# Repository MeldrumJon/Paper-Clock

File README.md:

# Paper-Clock

Minimalistic clock with an e-ink display.

## Components

- [Enclosure](./3D)
- [PCB](./hardware)
- [Firmware](./src)

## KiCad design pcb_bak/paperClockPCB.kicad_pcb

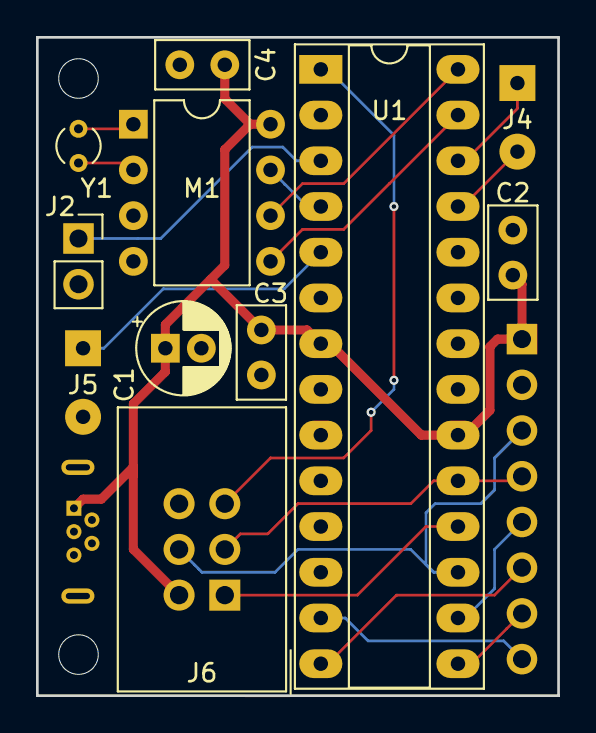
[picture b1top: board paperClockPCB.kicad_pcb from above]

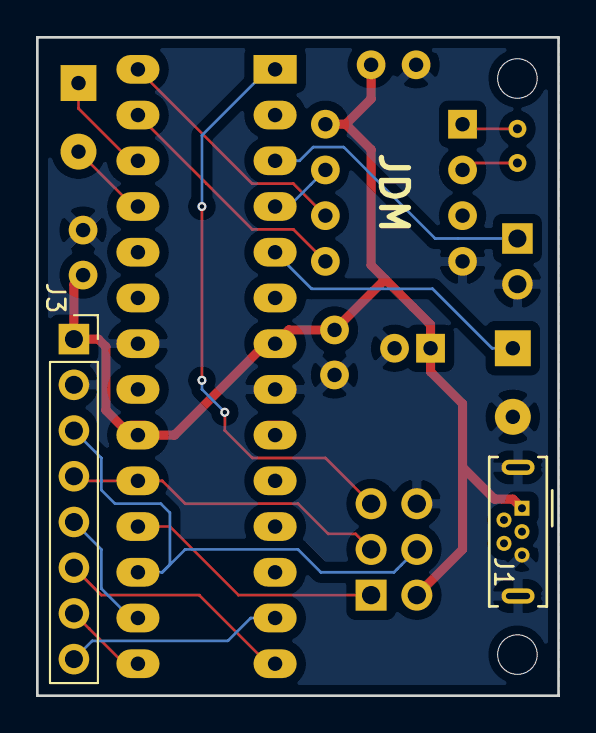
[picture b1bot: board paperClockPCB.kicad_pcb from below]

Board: 2 copper layers, 29.0 x 36.6 mm, 13 parts (2 on the bottom side), 19 nets.

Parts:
C1: 10u; CP_Radial_D5.0mm_P2.00mm
C2, C3, C4: 0.1u; C_Disc_D5.0mm_W2.5mm_P2.50mm
J1: USB_B_Micro; USB_Micro-B_Wuerth_614105150721_Vertical
J2: Conn_01x02_Female; PinSocket_1x02_P2.54mm_Vertical
J3: Conn_01x08; PinSocket_1x08_P2.54mm_Vertical
J4, J5: Conn_01x02; SolderWirePad_1x02_P3.81mm_Drill0.8mm
J6: AVR-ISP-6; IDC-Header_2x03_P2.54mm_Vertical
M1: DS1337; DIP-8_W7.62mm
U1: ATmega328P-PU; DIP-28_W7.62mm_Socket_LongPads
Y1: Crystal; Crystal_C26-LF_D2.1mm_L6.5mm_Vertical

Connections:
/BUSY: J3.8, U1.13
/CLK: J3.4, J6.3, U1.19
/CS: J3.5, U1.16
/DC: J3.6, U1.14
/DIN: J3.3, J6.4, U1.17
/INTB: M1.7, U1.4
/RST: J3.7, U1.15
/TX: J2.1, U1.3
GND: C1.2, C2.2, C3.1, C4.2, J1.5, J1.6, J2.2, J3.2, J5.2, J6.6, M1.4, U1.8, U1.22
unnamed: J4.1, U1.26
unnamed: J4.2, U1.25
unnamed: J5.1, U1.5
unnamed: J6.1, U1.18
unnamed: J6.5, U1.1
unnamed: M1.1, Y1.1
unnamed: M1.2, Y1.2
unnamed: M1.5, U1.27
unnamed: M1.6, U1.28
VCC: C1.1, C2.1, C3.2, C4.1, J1.1, J3.1, J6.2, M1.8, U1.7, U1.20

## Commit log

2019-08-16 Beginning Tests
2019-08-17 Hello world for a clock
2019-08-17 Arduino U8G2
    (switching to standalone C)
2019-08-17 Scrapped b/c no HW spi support
2019-08-17 Revert "Arduino U8G2"
    This reverts commit fea71a2b21564d61849765bd730da9470b42badc.
2019-08-18 Switch Libraries, Partial Update Working
2019-08-19 Almost ready to print
    Must figure out why it doesn't call disp_time();
2019-08-20 Improved Makefile
2019-08-20 Working!
2019-08-21 Display Works, Switch to GxEPD2
2019-08-31 Latest changes
2019-09-03 Some optimizations
2019-09-04 Encoder and button working.
2019-09-07 Ability to set clock, 24-hour time mode
2019-09-11 PCB project
2019-09-11 PCB v0.1
2019-09-11 Include 3rd Party Libraries
2019-09-11 Link to 3rd Party Libraries
2019-09-12 Parts List
2019-09-12 Added images
2019-09-13 Add setup and programming instructions
2019-09-15 Beginning Enclosure
2019-09-16 Code Reorganization
2019-09-17 Enclosure with guides
2019-09-17 Outside structure
2019-09-21 Nearly Completed Box
2019-10-12 Make model smaller, ordered print.
2019-10-27 Improve Look of Date/Time Setting
2019-11-09 Improve User-Interface for Setting Date/Time
2019-11-09 Rename PCB Folder
2019-11-09 Photos of Enclosure
2019-11-09 Update READMEs
2019-11-09 Update Enclosure README
2019-11-09 Improved Enclosure
    Make Threaded Inserts easier to insert
2019-11-09 Add Link to Enclosure on Shapeways
2019-11-09 Link to OSHPark PCB
2019-11-10 Clock with Bigger Fonts
2019-11-10 Optimizations
2019-11-10 Update Adafruit-GFX Library
2019-11-10 Update U8G2
2019-11-10 Update GxEPD2 Library
2019-11-10 Power Saving While Screen is Busy
2019-11-10 Update Libraries; Power Saving While Waiting for Screen
2019-11-10 Use a Square to Indicate PM, not invertred colors
2019-11-16 Update disp.cpp
    Larger PM indicator, only do a full refresh every 30 minutes.
2020-02-11 Reorganize
2020-02-23 Update Documentation
